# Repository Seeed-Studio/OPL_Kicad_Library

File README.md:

# Welcome to Our Hardware Component Repository!

Dive into a world of innovation with our curated collection of hardware components straight from the electronics hub of Shenzhen, complemented by an array of parts supported by Seeed Studio. Our mission is to empower makers, developers, and hardware enthusiasts with a diverse repository that streamlines innovation and accelerates development.

The Seeed Fusion Open Parts Libraries (OPL) and the associated component libraries are provided and maintained by the [Seeed Studio Fusion](https://www.seeedstudio.com/fusion.html) team and the wider community for the turnkey [Seeed Fusion PCB Assembly (PCBA) Service](https://www.seeedstudio.com/fusion_pcb.html).

**The XIAO Family**

To accelerate PCB design and make it much more convenient, Seeed Fusion has provided these component libraries for KiCad. Prepared and scrutinized by our own engineers, these footprints can save you hours of design time and minimize potential production errors, so you can get on with PCB design with peace of mind.

## Highlights(Content of Tables)

- [**Preparatory Work: KiCad Download and Library Download**](#jump1)
- [**How to add and use Seeed OPL Footprint Libraries(Grove Vision AI V2)**](#jump2)
- [**How to add and use Seeed OPL Symbol Libraries(Grove Vision AI V2)**](#jump3)
- [**Scale up Your Creation With Seeed Studio Fusion**](#jump4)
- [**Co-Create with Seeed Studio**](#jump5)
- [**Resources**](#jump6)

## <span id="jump1">Preparatory Work: KiCad Download and Library Download </span>

1. You can refer to this [link](https://www.kicad.org/download/) to download the KiCad software.

2. You can [download](https://github.com/Seeed-Studio/OPL_Kicad_Library) the "OPL_KiCad_Library" or use command to clone:

```
git clone https://github.com/Seeed-Studio/OPL_Kicad_Library.git
```

## How to add and use Seeed OPL Footprint Libraries

### <span id="jump2"> Take Grove Vision AI V2 and XIAO footprint as an Example </span>

1. Open KiCad and refer to `File -> Open Project`.

2. Find the "Grove Vision AI V2 Library" and open the project:

3. Double click the "Grove Vision AI V2" PCB file and you will see below:

4. Refer to the `Preferences -> Manage Footprint Libraries`

5. Here is the existed footprint libraries and you can click the button below:

6. Find the "Grove Vision AI V2 Library" and open the folder that contains the boards footprint:

Now you have added the "XIAO footprint library"

7. You can click here to use the added library:

8. Search for "seeed" and you can check the footprint added:

9. Click "ok" and you can add the XIAO RP2040 footprint into the "Grove Vision VI V2".

10. You can change any component on the Grove Vision VI V2 module and make it your own project.

## <span id="jump3"> How to add and use Seeed OPL Symbol Libraries </span>

### Take Grove Vision AI V2 and Sensor-Transducer as an Example:

1. Open KiCad and refer to `File -> Open Project`.

2. Find the "Grove Vision AI V2 Library" and open the project:

3. Double click the "Grove Vision AI V2" .sch file and you will see below:

4. Refer to the `Preferences -> Manage Symbol Libraries`

5. Here is the existed symbol libraries and you can click the button below:

6. Find the "OPL_Sensor-Transducer" lib file:

Now you have added the "OPL_Sensor-Transducer library"

7. You can click here to use the added library:

8. Search for "OPL" and you can check the symbol added:

9. Click "ok" and you can add it into the "Grove Vision VI V2".

10. You can change any component on the Grove Vision VI V2 module and make it your own project.

## <span id="jump4"> Scale up Your Creation With Seeed Studio Fusion </span>

Seeed Studio Fusion serves as the comprehensive service platform for Seeed Studio, a global one-stop online platform offering PCB manufacturing, PCB assembly and hardware customization with global sourcing capability. Whether you need prototyping, mass production, custom solutions for open-source products, or the transformation of your creative ideas into profitable products, Seeed Studio Fusion can meet your requirements.

- [PCB/PCBA Design](https://www.seeedstudio.com/fusion_pcb.html)
- [Fusion Website](https://www.seeedstudio.com/fusion.html)
- **Email Contact**: fusion@seeed.io

## <span id="jump5"> Co-Create with Seeed Studio </span>

Leverage our Co-Create Program to transform your advanced prototype into a commercially successful product! This program is designed to optimize your product's journey from prototype to market by handling marketing, packaging, and distribution, allowing you to concentrate on refining your product. Upon acceptance of your prototype by Seeed, it will be showcased on the Seeed Studio marketplace. You'll receive a portion of the profits for each unit sold.

- [Application Form](https://docs.google.com/forms/d/e/1FAIpQLSe3A7_rIbn2OLO4JyJd_poGZodItCaRy6M6-3FtdqL3xG1Usg/viewform)
- [Co-Create Website](https://www.seeedstudio.com/co-create.html)

## <span id="jump6"> Resources </span>

- [Seeed Studio Open Parts List](https://files.seeedstudio.com/wiki/OPL/OPL_list.xlsx)

<!-- ## Even More Components!

As of last December, the [OPL has expanded](http://www.seeedstudio.com/blog/2018/12/04/just-what-you-wanted-for-xmas-introducing-the-new-shenzhen-open-parts-library-with-over-10000-parts/) from 800 components to more than 10,000 with the introduction of the new Shenzhen OPL. The original Seeed OPL is a catalog of components from Seeed’s own inventory, we have the parts and, we have been using them in our own production processes for years. The Shenzhen OPL contains parts from Shenzhen’s biggest components distributor that Seeed can quickly order for turnkey PCBA. While the sources are different, both can be used together with the Seeed Fusion PCBA service and reduce the production time to 7 days.

But with all the new components and many more to come, we don’t have enough resources to create the footprints for all of them. So, we are asking for help from you and the wider community to gradually build-up the library with us. As more and more users utilize the OPL and update the component libraries, the better the library will become for everyone. 

To assist with the process, we have designated a team of engineers to maintain the library and GitHub repositories. They will also help draw some footprints and connect schematic symbols. But while our engineers do their best to check each footprint, with the sheer number of components, it is inevitable that some errors will be present. It is unavoidable. So to make up for it, Seeed Fusion has introduced a re-manufacture promise: If an error in the library requires the boards to be re-manufactured, then we will re-manufacture the corrected boards for you for free. By using this library, you accept this potential risk.

## Footprint Design Guidelines
It is still early days, and we have a lot of catching up to do. So, the most important additions at this stage are unique symbols and footprints and any generic footprints that are missing. Part-specific symbols that use generic footprints and slight variations of generic footprints can be added later.

For consistency and ease of use, we would greatly appreciate it if everyone followed the same guidelines for new additions to the library:

-	The previous component libraries have been re-organized to match the Shenzhen OPL’s categorization. Please add new entries to the relevant sub-library according to the online OPL library’s classification.
-	Please take the time to study [KiCad’s own Library Convention](http://kicad-pcb.org/libraries/klc/) and ensure that the new footprints comply. Please refer to other footprints in the OPL or KiCad’s built-in footprints for reference. 
-	For MPN specific footprints, please follow the existing footprint naming convention for the footprint and name the corresponding schematic symbol with the manufacturer part number.

### Notes:
- #### The current version of the KiCad Library has been completely revamped in response to all the feedback we have recieved. Originally a direct import of the Eagle library, the old library did not comply with KiCad guidelines and placed features on the wrong layers. For the latest version, we have throroughly investigated the issues and revised (nearly) all of the footprints. Let us know if you think we missed something!

-	The Seeed OPL component libraries have been updated to match the Shenzhen OPL categories to aid in merging the two libraries. Some components will have moved to new homes, but this has not been updated on the website OPL library yet. We will update this soon!
-	Some of the original Seeed OPL KiCad component footprints have not been updated to match KiCad’s design guidelines yet. They are safe to use, and the pads are correct, but they may look a little ugly.
-	Unlike previous versions, we have uploaded the files individually as opposed to a whole zip file. We hope this will help you follow standard GitHub workflow to contribute changes. (Thanks for your feedback!)

There is a lot to consider in managing a large library like this, so we would greatly appreciate any ideas and feedback regarding how we can make the library more user-friendly. We’ll be monitoring the discussion section and the designated OPL section in our forums. You are also welcome to let us know by [e-mail](mailto:fusion@seeed.cc).

We hope the new maintained library will prove to be an invaluable resource to all of our PCBA users and beyond.

## Resources
1. A KiCad Bill-of-Materials (BOM) plugin to follow SeeedStudio's Fusion PCBA assembly service's template, This plugin is set up to use the KiCad schematic's part data as it is provided in Seeed Studio's Open Parts Library (OPL) collection for KiCad. - https://github.com/imrehg/kicad-bom-seeedstudio

 -->

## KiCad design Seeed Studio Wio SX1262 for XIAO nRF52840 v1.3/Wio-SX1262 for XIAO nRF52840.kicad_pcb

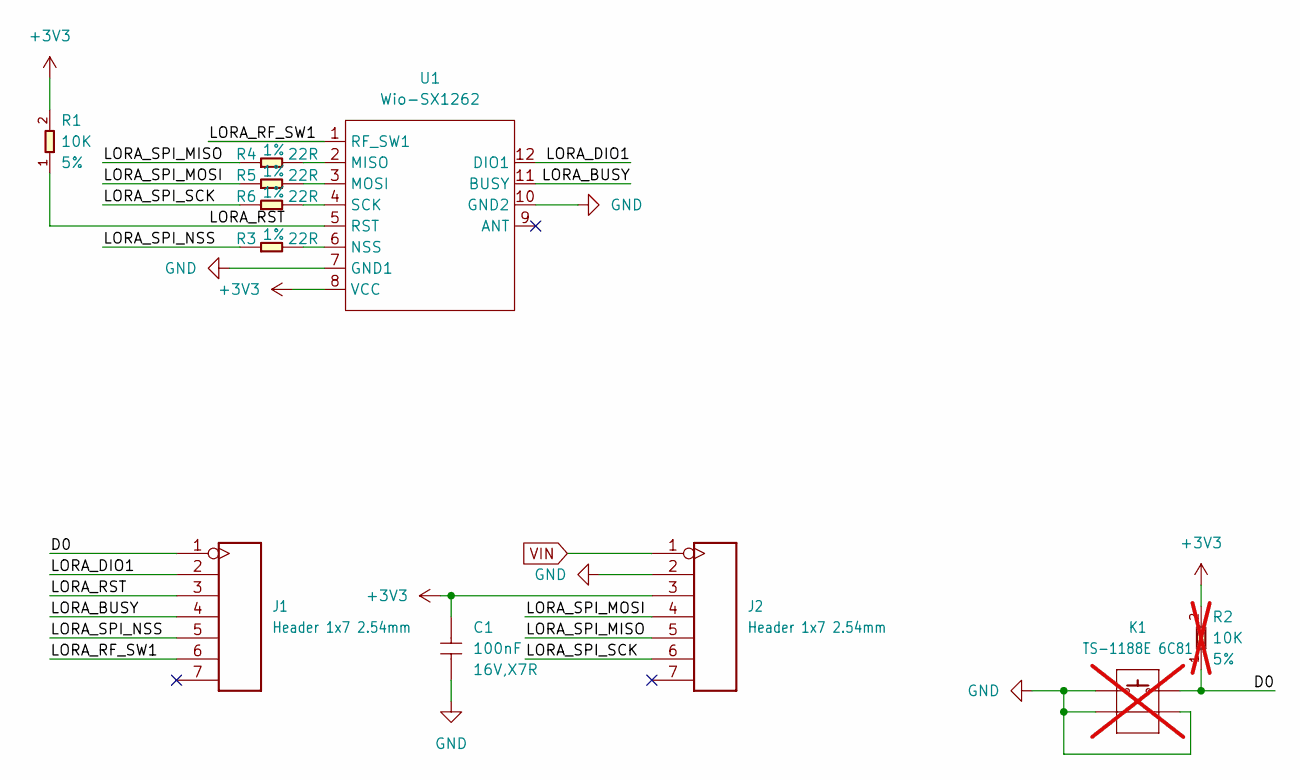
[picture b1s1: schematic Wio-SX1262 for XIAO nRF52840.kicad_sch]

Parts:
C1: 100nF; C0402; Voltage Rating 16V,X7R; MPN CC0402KRX7R7BB104
J1, J2: Header 1x7 2.54mm; H7-2.54; Part Type Header
K1: TS-1188E 6C81; SW4-SMD-7.0X3.5X3.5MM-90D; MPN TS-1188E 6C81; not fitted
R1: 10K; R0402; Power Rating 5%; MPN RC0402JR-0710KL
R2: 10K; R0402; Power Rating 5%; MPN RC0402JR-0710KL; not fitted
R3, R4, R5, R6: 22R; R0402; Power Rating 1%; MPN RC0402FR-0722RL
U1: Wio-SX1262; MODULE12P-1.27-11X11.6MM; MPN Wio-SX1262

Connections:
+3V3: C1.1, J2.3, R1.2, R2.2, U1.8 (VCC)
/D0: J1.1, K1.2, R2.1
/LORA_BUSY: J1.4, U1.11 (BUSY)
/LORA_DIO1: J1.2, U1.12 (DIO1)
/LORA_RF_SW1: J1.6, U1.1 (RF_SW1)
/LORA_RST: J1.3, R1.1, U1.5 (RST)
/LORA_SPI_MISO: J2.5, R4.1
/LORA_SPI_MOSI: J2.4, R5.1
/LORA_SPI_NSS: J1.5, R3.1
/LORA_SPI_SCK: J2.6, R6.1
GND: C1.2, J2.2, K1.1, K1.3 (S1), K1.4 (S2), U1.7 (GND1), U1.10 (GND2)
unnamed: R4.2, U1.2 (MISO)
unnamed: R5.2, U1.3 (MOSI)
unnamed: R3.2, U1.6 (NSS)
unnamed: R6.2, U1.4 (SCK)
VIN: J2.1

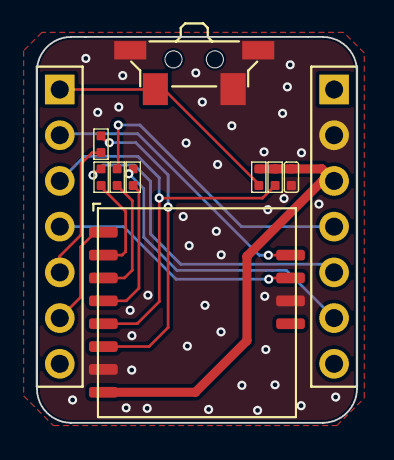
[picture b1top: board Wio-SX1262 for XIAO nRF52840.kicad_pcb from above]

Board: 2 copper layers, 17.8 x 21.4 mm, 11 parts (0 on the bottom side), 15 nets.

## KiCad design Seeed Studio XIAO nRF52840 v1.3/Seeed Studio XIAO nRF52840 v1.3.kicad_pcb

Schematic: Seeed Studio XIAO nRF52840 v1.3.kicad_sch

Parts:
ANT1: ANTENNA-AN3216; ANT-SMD3P-3.2X1.6X1.04MM
BAT0: TEST-POINT'4080'; TP-80X40MIL
C1, C5, C8, C24, C34: 100nF; C0201
C2, C7: 10pF; C0201
C3, C4, C6, C9, C22, C25, C29, C30, C39, C41, C42: 2.2uF; C0201
C10: 1nF; C0402
C11: 1pF; C0201
C31: 820pF; C0201
C32, C33: 15pF; C0201
C35: 100pF; C0201
C36: 0.8pF; C0201
C37: 0.5pF; C0201
C38: 4.7nH; L0201
C40: DNP; C0201
CHG0: RED; LED-0402
D1: DIODE'0603'; SOD-523
GND0: GND; TP-80X40MIL
J1, J2: DNP; H7-HALF-HOLE-2.54
K1: BUTTON-4P; SW4-SMD-2.8-2.6X1.6X0.53MM
L3: 10uH; L0603
MIC1: MSM261D3526H1CPM; MIC6P-3.5X2.65X0.94MM
NFC1, NFC2: TEST-POINT'4080'; TP-80X40MIL
Q1: PMOS_1.00.60.35MM; PMOS_1.0_0.6_0.35MM
R1, R2: 5.1k; R0201
R3, R5, R7: 2.2k; R0201
R4, R13, R14, R15, R20: 10k; R0201
R9: 100k; R0201
R10, R11: 33R; R0201
R12, R18: 2.7k; R0201
R16: 1M_1%; R0201
R17: 510k_1%; R0201
RGB6: RGB; 4P1010
TP1, TP2, TP3, TP5: TEST-POINT'4545'; TP-D45MIL
U1: NRF52840_QF; AQFN50P700X700X85_HS-74N
U2: BQ25100; BQ25101_DSBGA_6_BQ25101
U3: LSM6DS3TR-C; LGA14-0.5-2.5X3X0.86MM
U6: 3.3V; X2SON-4
U7: DNP; USON2X3_8
USB1: USB2.0-TYPE-C
X1: 32.768KHz; X2-SMD-L1.6X1.0X0.5MM
X2: 32MHz; 4P1612

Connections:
3V3: C3.2, C6.2, C29.2, C39.1, C41.2, J1.5, J1.17 (5), R5.1, R13.1, RGB6.+, U1.A22 (VDD@A22), U1.AD14 (VDD@AD14), U1.AD23 (VDD@AD23), U1.B1 (VDD@B1), U1.W1 (VDD@W1), U1.Y2 (VDDH@Y2), U6.1 (OUT), U7.8 (VCC)
6D_INT1: U1.T2 (P0.11@T2), U3.4 (INT1)
6D_PWR: C1.2, R14.1, R15.1, U1.P2 (P1.08@P2), U3.5 (VDDIO), U3.8 (VDD), U3.12 (CS)
/CE: R20.1, U2.B1 (TS)
DEC4-6: C34.1, C42.1, L3.2, U1.B5 (DEC4@B5), U1.E24 (DEC6@E24)
GND: ANT1.2 (GND), C1.1, C2.1, C3.1, C4.2, C5.2, C6.1, C7.1, C8.1, C9.1, C10.2, C11.1, C22.1, C24.1, C25.1, C29.1, C30.2, C31.2, C32.2, C33.2, C34.2, C35.2, C36.1, C37.1, C39.2, C40.2, C41.1, C42.2, GND0.1, J1.6, J1.18 (6), K1.2 (B0), K1.4 (B1), MIC1.4 (GND@1), MIC1.5 (L/R), MIC1.6 (GND@2), R1.2, R2.1, R9.1, R18.2, R20.2, TP1.T, U1.B7 (VSS@B7), U1.F23 (VSS_PA@F23), U1.G74 (VSS_PAD), U2.C2 (VSS), U3.1 (SDO/DA0), U3.2 (SDX), U3.3 (SCX), U3.6 (GND@1), U3.7 (GND@2), U6.2 (GND), U6.T (GND), U7.4 (GND), U7.PAD (T), USB1.A1_B12 (A1/B12/GND), USB1.B1_A12 (B1/A12/GND), USB1.S1, USB1.S2, USB1.S3, USB1.S4, USB1.S5 (S1), USB1.S6 (S2), X2.2 (1), X2.4 (3)
INTERNAL_I2C_SCL: R14.2, U1.H2 (P0.27@H2), U3.13 (SCL)
INTERNAL_I2C_SDA: R15.2, U1.M2 (P0.07@M2), U3.14 (SDA)
unnamed: R1.1, USB1.A5 (A5/CC1)
unnamed: R2.2, USB1.B5 (B5/CC2)
unnamed: C2.2, U1.D2 (P0.00/XL1@D2), X1.2
unnamed: C7.2, U1.F2 (P0.01/XL2@F2), X1.1
unnamed: R7.1, RGB6.R-
unnamed: R4.1, RGB6.G-
unnamed: R10.2, U1.AD4 (D-@AD4)
unnamed: R11.2, U1.AD6 (D+@AD6)
unnamed: R3.1, RGB6.B-
unnamed: CHG0.+, R5.2
unnamed: ANT1.3, C10.1
unnamed: R12.1, R18.1, U2.B2 (ISET)
unnamed: C22.2, U1.AC5 (DECUSB@AC5)
unnamed: C24.2, U1.C1 (DEC1@C1)
unnamed: C31.1, U1.N24 (DEC5@N24)
unnamed: C33.1, U1.B24 (XC1@B24), X2.1 (2)
unnamed: C32.1, U1.A23 (XC2@A23), X2.3 (4)
unnamed: C35.1, U1.D23 (DEC3@D23)
unnamed: C36.2, C38.1, U1.H23 (ANT@H23)
unnamed: ANT1.1 (S), C37.2, C38.2
unnamed: C40.1, U1.A18 (DEC2@A18)
unnamed: L3.1, U1.B3 (DCC@B3)
P0.02_AIN0_LOW_A0_D0: J2.1, J2.13 (1), U1.A12 (P0.02/AIN0@A12)
P0.03_AIN1_LOW_A1_D1: J2.2, J2.14 (2), U1.B13 (P0.03/AIN1@B13)
P0.04_AIN2_A4_D4: J2.5, J2.17 (5), U1.J1 (P0.04/AIN2@J1)
P0.05_AIN3_A5_D5: J2.6, J2.18 (6), U1.K2 (P0.05/AIN3@K2)
P0.06_USER_BLUE: R3.2, U1.L1 (P0.06@L1)
P0.09/NFC1: NFC1.1, U1.L24 (P0.09/NFC1@L24)
P0.10/NFC2: NFC2.1, U1.J24 (P0.10/NFC2@J24)
P0.13_HICHG: R12.2, U1.AD8 (P0.13@AD8)
P0.14_~READ_BAT: R17.2, U1.AC9 (P0.14@AC9)
P0.16_PDM_DATA: MIC1.3 (DATA), U1.AC11 (P0.16@AC11)
P0.17_~CHG: CHG0.-, U1.AD12 (P0.17@AD12), U2.C1 (PRETERM)
P0.20_QSPI_SIO_0: U1.AD16 (P0.20@AD16), U7.5 (DI)
P0.21_QSPI_SCK: C11.2, U1.AC17 (P0.21@AC17), U7.6 (CLK)
P0.22_QSPI_SIO_2: U1.AD18 (P0.22@AD18), U7.3 (~WP)
P0.23_QSPI_SIO_3: U1.AC19 (P0.23@AC19), U7.7 (~HOLD)
P0.24_QSPI_SIO_1: U1.AD20 (P0.24@AD20), U7.2 (DO)
P0.25_QSPI_CSN: U1.AC21 (P0.25@AC21), U7.1 (~CS)
P0.26_USER_RED: R7.2, U1.G1 (P0.26@G1)
P0.28_AIN4_LOW_A2_D2: J2.3, J2.15 (3), U1.B11 (P0.28/AIN4@B11)
P0.29_AIN5_LOW_A3_D3: J2.4, J2.16 (4), U1.A10 (P0.29/AIN5@A10)
P0.30_USER_GREEN: R4.2, U1.B9 (P0.30/AIN6@B9)
P0.31_AIN7_BAT: R16.2, R17.1, U1.A8 (P0.31/AIN7@A8)
P1.00_PDM_CLK: MIC1.2 (CLK), U1.AD22 (P1.00@AD22)
P1.10_MIC_PWR: C8.2, MIC1.1 (VDD), U1.A20 (P1.10@A20)
P1.11_TX_D6: J2.7, J2.19 (7), U1.B19 (P1.11@B19)
P1.12_RX_D7: J1.1, J1.13 (1), U1.B17 (P1.12@B17)
P1.13_SCK_D8: J1.2, J1.14 (2), U1.A16 (P1.13@A16)
P1.14_MISO_D9: J1.3, J1.15 (3), U1.B15 (P1.14@B15)
P1.15_MOSI_D10: J1.4, J1.16 (4), U1.A14 (P1.15@A14)
PWR_LED: U1.R24 (P1.06@R24)
RESET: C5.1, K1.1 (A0), K1.3 (A1), R13.2, TP2.T, U1.AC13 (P0.18/RESET@AC13)
SWDCLK: TP3.T, U1.AA24 (SWDCLK@AA24)
SWDIO: TP5.T, U1.AC24 (SWDIO@AC24)
USB_D+: R11.1, USB1.A6 (A6/DP1), USB1.B6 (B6/DP2)
USB_D-: R10.1, USB1.A7 (A7/DN1), USB1.B7 (B7/DN2)
VBAT: BAT0.1, C30.1, Q1.1 (D), R16.1, U2.A1 (OUT)
VBUS: C9.2, C25.2, D1.+, J1.7, J1.19 (7), Q1.2 (G), R9.2, U1.AD2 (VBUS@AD2), U2.A2 (IN), USB1.A4_B9 (A4/B9/VBUS), USB1.B4_A9 (B4/A9/VBUS)
VIN: C4.1, D1.-, Q1.3 (S), U6.3 (EN), U6.4 (IN)

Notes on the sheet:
Linus.Liao
2.Change C32,C33 to 15pF
zhihuai.Zhou
Initail Version
the TS and VSS.
NTC:
2021.2.2
Set P0.14 to output Sink only to enable BAT voltage read;
v1.0
2.Add C11 to to resolve the issue of data corruption during Flash read operations.
1.Change 32M Crystal
Disable Temp sense function,
2025.6.20
1.Remove R8
use fixed 10k resistor between
2024.3.19

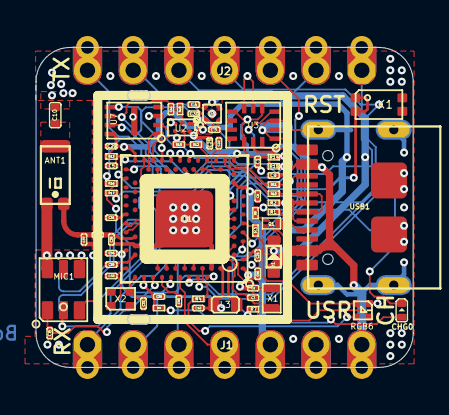
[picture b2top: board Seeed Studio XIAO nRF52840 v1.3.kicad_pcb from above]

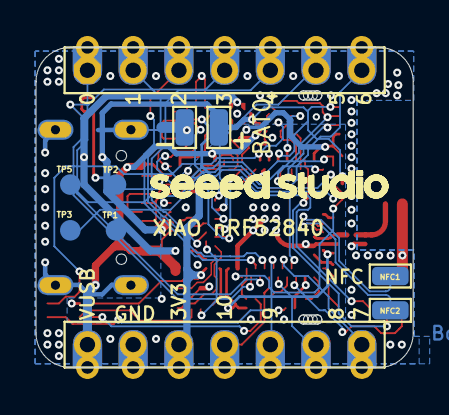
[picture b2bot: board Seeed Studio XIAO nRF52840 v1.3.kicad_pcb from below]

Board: 2 copper layers, 21.0 x 17.8 mm, 80 parts (9 on the bottom side), 67 nets.

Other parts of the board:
U$14: LOGO-SEEED-NEW-1_3X13MM
UNK_HOLE_0: dummyfp0
UNK_HOLE_1: dummyfp1
UNK_HOLE_2: dummyfp2
UNK_HOLE_3: dummyfp3
UNK_HOLE_4: dummyfp4
UNK_HOLE_5: dummyfp5
UNK_HOLE_6: dummyfp6
UNK_HOLE_7: dummyfp7

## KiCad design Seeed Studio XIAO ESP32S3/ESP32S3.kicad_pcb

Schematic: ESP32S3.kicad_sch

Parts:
ANT1: U.FL-R-SMT-1; U-FL3P-SMD-2.6X2.6X1.0MM
BAT0: VBAT; TP-80X40MIL
C1, C2, C17, C20: DNP; C0201
C3, C9, C13, C16: 2.2uF; C0201
C4, C5, C6: 4.7uF; C0201
C7, C8, C28: 10pF; C0201
C10, C21, C25, C26: 1uF; C0201
C11, C14, C15, C19, C22, C23, C29, C30: 100nF; C0201
C12: 10nF; C0201
C18: 1pF; C0201
CHG0: RED; LED-0402
D2: LMBR4010BST5G; DFN1006-2L
D3: Yellow; LED-0402
GND0: GND; TP-80X40MIL
J1, J2: DNP; H7-HALF-HOLE-2.54
J3: DF40C-30DP-0.4V(51); BTB30-0.4-7.52X2.97X1.14
K1, K2: SKTAAAE010/311021459; SW4-SMD-2.8-2.6X1.6X0.53MM
L1: 2nH; L0201
L2: 3.3nH; L0201
L3: DNP; L0201
L4: 470nH; L0603
Q1: LP0404N3T5G; PMOS_1.0_0.6_0.35MM
R1, R2: 5.1K; R0201
R3, R4: 22R; R0201
R5: 0R; R0201
R6: 499R; R0201
R7, R8, R11: 10K; R0201
R9: 100K; C0201
R10: 220K; R0201
R13: 249K; R0201
R15: 1.5K; R0201
TP1, TP2, TP3, TP4, TP5, TP6, TP7, TP8: TEST-POINT'4545'; TP-D45MIL
U1: ESP32-S3R8; QFN56G-0.4-7X7MM
U3: SGM6029CYG/TR; BGA6-0.35-0.745X10.95X0.4MM
U4: SGM40567-4.2XG/TR; WLCSP-0.4-0.92X1.16X0.4MM
U5: GD25Q64ENIGR; USON8-0.8-4X3MM
USB0: UBF31-0171; USB2.0-TYPE-C
X1: 40MHz/306011364; X4-SMD-1.6X1.2X0.35MM

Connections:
D0/A0: J2.1, J2.13 (1), U1.6 (GPIO1)
D1/A1: J2.2, J2.14 (2), U1.7 (GPIO2)
D2/A2: J2.3, J2.15 (3), J3.2, U1.8 (GPIO3)
D3/A3: J2.4, J2.16 (4), U1.9 (GPIO4)
D4/I2C_SDA: J2.5, J2.17 (5), U1.10 (GPIO5)
D5/I2C_SCL: J2.6, J2.18 (6), U1.11 (GPIO6)
D6/TX: J2.7, J2.19 (7), R6.2
D7/RX: J1.1, J1.13 (1), U1.50 (U0RXD)
D8/A8/SCK: J1.2, J1.14 (2), J3.3, U1.12 (GPIO7)
D9/A9/MISO: J1.3, J1.15 (3), J3.4, U1.13 (GPIO8)
D10/A10/MOSI: J1.4, J1.16 (4), J3.5, U1.14 (GPIO9)
EN: C21.2, K1.1 (A0), K1.3 (A1), R8.1, TP6.T, U1.4 (CHIP_PU)
ESP_USB_D+: C1.2, R4.2, TP8.T, U1.26 (GPIO20)
ESP_USB_D-: C2.2, R3.2, TP7.T, U1.25 (GPIO19)
GND: ANT1.GND1, ANT1.GND2, C1.1, C2.1, C3.2, C4.2, C5.1, C6.1, C7.2, C8.1, C9.1, C10.2, C11.1, C12.1, C13.1, C14.1, C15.1, C16.1, C17.1, C18.1, C19.1, C20.1, C21.1, C22.1, C23.2, C25.2, C26.2, C28.1, C29.1, C30.1, GND0.1, J1.6, J1.18 (6), J3.1, J3.17, J3.28, J3.29, J3.31, J3.33, J3.34, K1.2 (B0), K1.4 (B1), K2.2 (B0), K2.4 (B1), R1.1, R2.2, R9.1, R10.1, R13.1, TP1.T, U1.57 (GND), U3.A1 (GND), U4.B1 (F), U4.C2 (GND), U5.4 (GND), USB0.A1_B12 (A1/B12/GND), USB0.B1_A12 (B1/A12/GND), USB0.S1, USB0.S2, USB0.S3, USB0.S4, USB0.S5 (S1), USB0.S6 (S2), X1.2 (GND), X1.4 (GND@1)
GND5: L4.1, U3.B2 (SW)
GND6: R13.2, U3.C1 (MODE)
GPIO0: C28.2, K2.1 (A0), K2.3 (A1), R7.1, U1.5 (GPIO0)
IO10/XMCLK: J3.6, U1.15 (GPIO10)
IO11/DVP_Y8: J3.7, U1.16 (GPIO11)
IO12/DVP_Y7: J3.8, U1.17 (GPIO12)
IO13/DVP_PCLK: J3.9, U1.18 (GPIO13)
IO14/DVP_Y6: J3.10, U1.19 (GPIO14)
IO15/DVP_Y2: J3.11, U1.21 (XTAL_32K_P)
IO16/DVP_Y5: J3.12, U1.22 (XTAL_32K_N)
IO17/DVP_Y3: J3.13, U1.23 (GPIO17)
IO18/DVP_Y4: J3.14, U1.24 (GPIO18)
IO21/USER_LED: D3.-, J3.16, U1.27 (GPIO21)
IO38/DVP_VSYNC: J3.23, U1.43 (GPIO38)
IO47/DVP_HREF: J3.22, U1.37 (SPICLK_P)
IO48/DVP_Y9: J3.21, U1.36 (SPICLK_N)
MTCK/IO39/CAM_SCL: J3.24, TP5.T, U1.44 (MTCK)
MTDI/IO41/PDM_DATA: J3.26, TP3.T, U1.47 (MTDI)
MTDO/IO40/CAM_SDA: J3.25, TP4.T, U1.45 (MTDO)
MTMS/IO42/PDM_CLK: J3.27, TP2.T, U1.48 (MTMS)
unnamed: R5.1, U1.54 (XTAL_P)
unnamed: C7.1, R5.2, X1.3 (X2)
unnamed: C8.2, U1.53 (XTAL_N), X1.1 (X1)
unnamed: ANT1.D, C17.2, L2.1, L3.2
unnamed: R2.1, USB0.B5 (B5/CC2)
unnamed: C15.2, L1.2, U1.2 (VDD3P3@1), U1.3 (VDD3P3@2)
unnamed: R1.2, USB0.A5 (A5/CC1)
unnamed: C18.2, L2.2, U1.1 (LNA_IN)
unnamed: CHG0.-, U4.B2 (NCHG)
unnamed: R6.1, U1.49 (U0TXD)
unnamed: R10.2, U4.C1 (IREF)
unnamed: CHG0.+, R11.2
unnamed: D3.+, R15.1
unnamed: C20.2, L3.1
SPICLK: U1.33 (SPICLK), U5.6 (CLK)
SPICS0: U1.32 (SPICS0), U5.1 (/CS)
SPID: U1.35 (SPID), U5.5 (DIO)
SPIHD: U1.30 (SPIHD), U5.7 (/HOLD)
SPIQ: U1.34 (SPIQ), U5.2 (DO)
SPIWP: U1.31 (SPIWP), U5.3 (/WP)
USB_D+: R4.1, USB0.A6 (A6/DP1), USB0.B6 (B6/DP2)
USB_D-: R3.1, USB0.A7 (A7/DN1), USB0.B7 (B7/DN2)
VBAT: BAT0.1, C26.1, Q1.1 (D), U4.A1 (BAT)
VBUS: C10.1, C25.1, D2.+, J1.7, J1.19 (7), Q1.2 (G), R9.2, R11.1, U4.A2 (VIN), USB0.A4_B9 (A4/B9/VBUS), USB0.B4_A9 (B4/A9/VBUS)
VCC_3V3: C5.2, C6.2, C9.2, C11.2, C12.2, C13.2, C14.2, C16.2, C19.2, C23.1, C29.2, J1.5, J1.17 (5), J3.18, J3.19, L1.1, L4.2, R7.2, R8.2, R15.2, U1.20 (VDD3P3_RTC), U1.46 (VDD3P3_CPU), U1.55 (VDDA@1), U1.56 (VDDA@2), U3.A2 (VOS)
VDD_SPI: C22.2, U1.29 (VDD_SPI), U5.8 (VCC)
VIN: C3.1, C4.1, C30.2, D2.-, J3.15, J3.30, Q1.3 (S), U3.B1 (VIN), U3.C2 (EN)

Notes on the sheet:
IO40
IO39
Π Type Impedance Matching
2.Adjust C30 and C16 inward
D0/A0/Qt1
DVP_Y7
Li Battery
IO5
External Flash
Optimize the distance from the positioning hole of the shield to the pads on both sides
DVP_Y3
D10/A10/Qt9/MOSI
0.3A/Pin
2023/1/4
LC Filter
IO1
D1/A1/Qt2
CAM
IO12
ESP32-S3
USB D+
Layout note： Bottom
D9/A9/Qt8/MISO
IO42
S3 IO20/D+
PDM_CLK
LCD
XIAO Header
v1.1
IO47
IO48
IO4
Camera
DVP_Y6
Internal PSRAM
IO21
IO11
BOOT
CAM_SCL
IO10

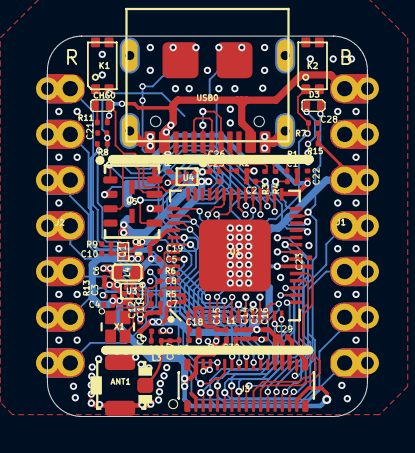
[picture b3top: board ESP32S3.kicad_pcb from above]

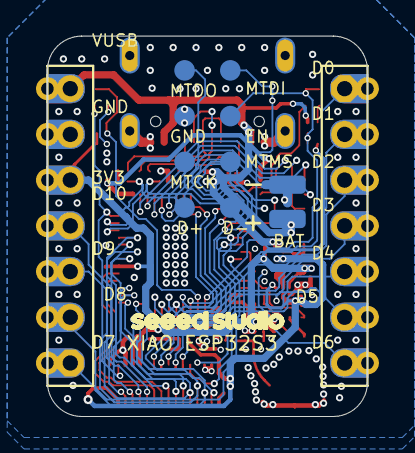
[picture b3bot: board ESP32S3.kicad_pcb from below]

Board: 2 copper layers, 17.8 x 21.1 mm, 72 parts (11 on the bottom side), 62 nets.

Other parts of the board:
U$7: LOGO-SEEED-NEW-0.94X8.4MM

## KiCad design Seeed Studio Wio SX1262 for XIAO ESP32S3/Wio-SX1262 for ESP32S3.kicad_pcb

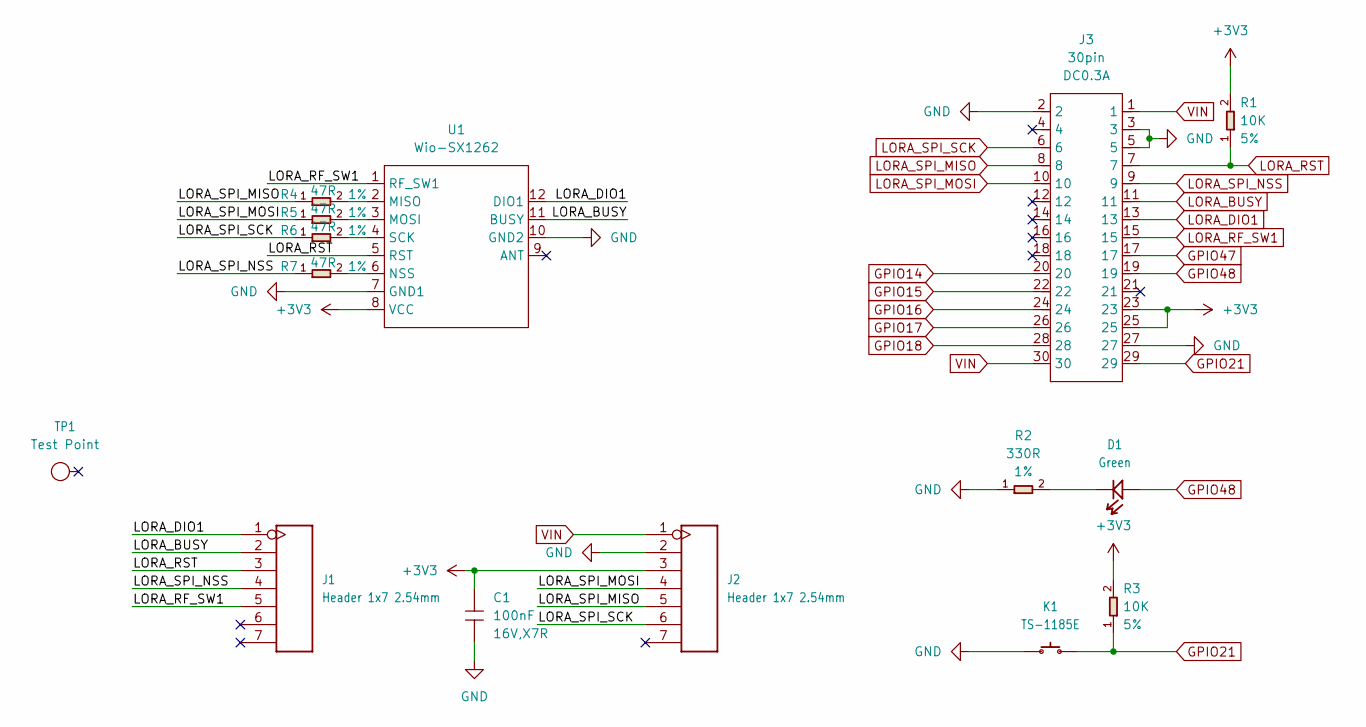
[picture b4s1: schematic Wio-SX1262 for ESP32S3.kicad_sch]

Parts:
C1: 100nF; C0402; Voltage Rating 16V,X7R; MPN CC0402KRX7R7BB104
D1: Green; LED-0603; MPN 19-217/G7C-AN1P2/3T
J1, J2: Header 1x7 2.54mm; H7-2.54; Part Type Header
J3: 30pin; BTB2X15-FEMALE-8.6X2.94X3.9MM; Rating DC0.3A; MPN BTB SCOKET P0.40
K1: TS-1185E; BUTTON2P_3_9X3X2MM; MPN TS-1185E
R1, R3: 10K; R0402; Power Rating 5%; MPN RC0402JR-0710KL
R2: 330R; R0402; Power Rating 1%; MPN RC0402FR-07330RL
R4, R5, R6, R7: 47R; R0402; Power Rating 1%; MPN RC0201FR-0745RL
TP1: Test Point; TP-D3_5c2_2mm; Part Type Test Point
U1: Wio-SX1262; MODULE12P-1.27-11X11.6MM; MPN Wio-SX1262

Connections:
+3V3: C1.1, J2.3, J3.23, J3.25, R1.2, R3.2, U1.8 (VCC)
GND: C1.2, J2.2, J3.2, J3.3, J3.5, J3.27, K1.1, R2.1, U1.7 (GND1), U1.10 (GND2)
GPIO14: J3.20
GPIO15: J3.22
GPIO16: J3.24
GPIO17: J3.26
GPIO18: J3.28
GPIO21: J3.29, K1.2, R3.1
GPIO47: J3.17
GPIO48: D1.1 (+), J3.19
LORA_BUSY: J1.2, J3.11, U1.11 (BUSY)
LORA_DIO1: J1.1, J3.13, U1.12 (DIO1)
LORA_RF_SW1: J1.5, J3.15, U1.1 (RF_SW1)
LORA_RST: J1.3, J3.7, R1.1, U1.5 (RST)
LORA_SPI_MISO: J2.5, J3.8, R4.1
LORA_SPI_MOSI: J2.4, J3.10, R5.1
LORA_SPI_NSS: J1.4, J3.9, R7.1
LORA_SPI_SCK: J2.6, J3.6, R6.1
unnamed: D1.2 (-), R2.2
unnamed: R4.2, U1.2 (MISO)
unnamed: R5.2, U1.3 (MOSI)
unnamed: R7.2, U1.6 (NSS)
unnamed: R6.2, U1.4 (SCK)
VIN: J2.1, J3.1, J3.30

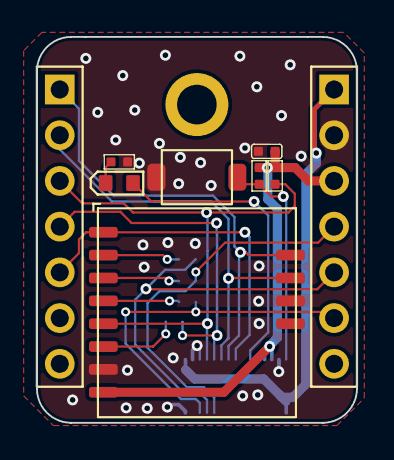
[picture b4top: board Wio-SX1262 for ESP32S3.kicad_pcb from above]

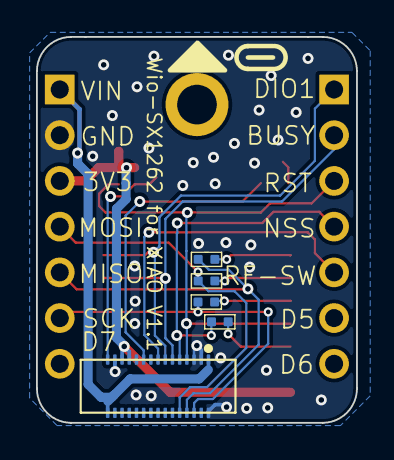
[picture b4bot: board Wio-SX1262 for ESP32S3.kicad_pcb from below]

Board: 2 copper layers, 17.8 x 21.4 mm, 15 parts (5 on the bottom side), 18 nets.

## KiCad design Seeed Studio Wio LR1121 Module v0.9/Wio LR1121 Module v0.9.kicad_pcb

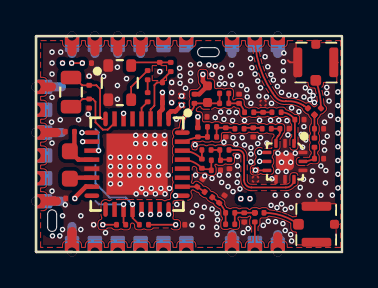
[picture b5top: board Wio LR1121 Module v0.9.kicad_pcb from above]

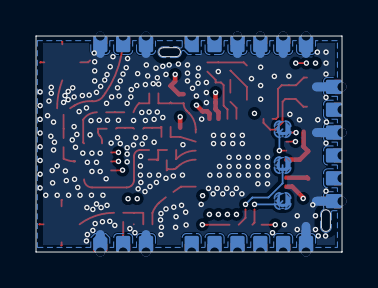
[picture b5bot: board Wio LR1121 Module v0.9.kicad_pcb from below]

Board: 4 copper layers, 17.0 x 12.0 mm, 69 parts (3 on the bottom side), 47 nets.

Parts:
C1, C2, C3, C4, C5, C6, C7, C8, C9, C11, C12, C13, C14, C15, C18, C19, C20, C22, C24, C25, C26, C27, C28, C29, C30, C31, C32, C33, C34, C35, C36, C37, C38, C39, C40, C41, C42, C43: C0201
FB1: L0201
J1, J2: U-FL4P-SMD-1_7X1_7X1_0MM
L1: L0402
L2, L3, L5, L6, L7, L8, L9, L10, L11, L13: L0201
L12: L0603
OSC1: X4_SMD_2_5X2_0MM
R1, R2, R3, R4, R5, R7, R8, R9: R0201
TP23, TP24, TP25: TP35S_SMD
U1: QFN12_0D5_2X2X0_55MM
U2: QFN32_0D5_5X5MM_EP3P3MM
U3: MODULE24_1D27_17X12MM
X1: X2_SMD_2X1_2MM

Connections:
2.4G_RF: C43.2, U3.2
GND_POWER: C3.2, C4.2, C5.2, C6.2, C7.2, C8.2, C11.2, C12.2, C13.2, C14.2, C15.2, C18.2, C19.2, C22.2, C25.2, C26.2, C28.2, C29.2, C30.2, C31.2, C32.2, C33.2, C35.2, C36.2, C37.2, C38.2, C40.2, C42.2, J1.2, J1.3, J1.4, J2.2, J2.3, J2.4, OSC1.1, OSC1.2, U1.2, U1.7, U1.8, U1.10, U1.12, U1.13, U2.13, U2.33, U3.1, U3.3, U3.9, U3.10, U3.13, U3.15, U3.16, U3.17, U3.18, U3.19, U3.22, U3.24
HP_LF: C1.1, L1.2, L2.1, R1.2, U2.32
LP_LF: C9.1, L6.1, L13.2, U2.31
LR1121_BUSY: U2.25, U3.8
LR1121_DIO8: U2.10, U3.11
LR1121_DIO9_INT: U2.9, U3.12
LR1121_RSTN: C42.1, R7.2, U2.6, U3.14
LR1121_SPI_MISO: U2.21, U3.7
LR1121_SPI_MOSI: U2.22, U3.6
LR1121_SPI_NSS: U2.24, U3.4
LR1121_SPI_SCK: U2.23, U3.5
MCU_DIO5: R3.1, TP23.1, U2.20
MCU_DIO6: R2.1, TP24.1, U2.19
MCU_DIO7: R5.1, TP25.1, U2.11
N18704063: C25.1, U2.7, X1.1
N18704080: C26.1, U2.8, X1.2
N18704168: L12.2, U2.14
N18704177: C31.1, L12.1, U2.12
N18704981: C9.2, C37.1, L6.2, L7.1
N18704990: C1.2, C3.1, L2.2, L3.1
N18705097: C2.1, C4.1, L3.2
N18705182: C38.1, C39.1, L7.2
N18705449: C18.1, C39.2, U1.3
N18705460: C2.2, C5.1, U1.1
N18706098: C20.2, C40.1, C41.1, L9.2
N18706198: C41.2, U1.9
N18706539: C24.1, C29.1, L10.2, L11.1
N18706650: C24.2, C27.1, C30.1, C43.1, L11.2
N18706671: C27.2, J2.1
N18712116: C14.1, L5.1, U1.11
N18712319: C36.1, FB1.2, OSC1.4
N18712325: C34.1, OSC1.3
N18712327: C34.2, R4.1
N18713044: C15.1, L5.2, R8.1, R9.1
N18751757: J1.1, R8.2
RFIO_HF: C28.1, L10.1, U2.26
RFI_N: C22.1, L8.2, L9.1, U2.29
RFI_P: C20.1, L8.1, U2.30
RFSW0_V1: C33.1, R3.2, U1.4
RFSW1_V2: C32.1, R2.2, U1.5
RFSW_VDD: C19.1, R5.2, U1.6
SUBG_RF: R9.2, U3.23
VDD_RF: C11.1, C12.1, C13.1, R7.1, U2.2, U2.15, U3.20, U3.21
VR_PA: C6.1, C7.1, C8.1, L1.1, L13.1, R1.1, U2.1
VTCXO: C35.1, FB1.1, U2.3
XTA: R4.2, U2.4
